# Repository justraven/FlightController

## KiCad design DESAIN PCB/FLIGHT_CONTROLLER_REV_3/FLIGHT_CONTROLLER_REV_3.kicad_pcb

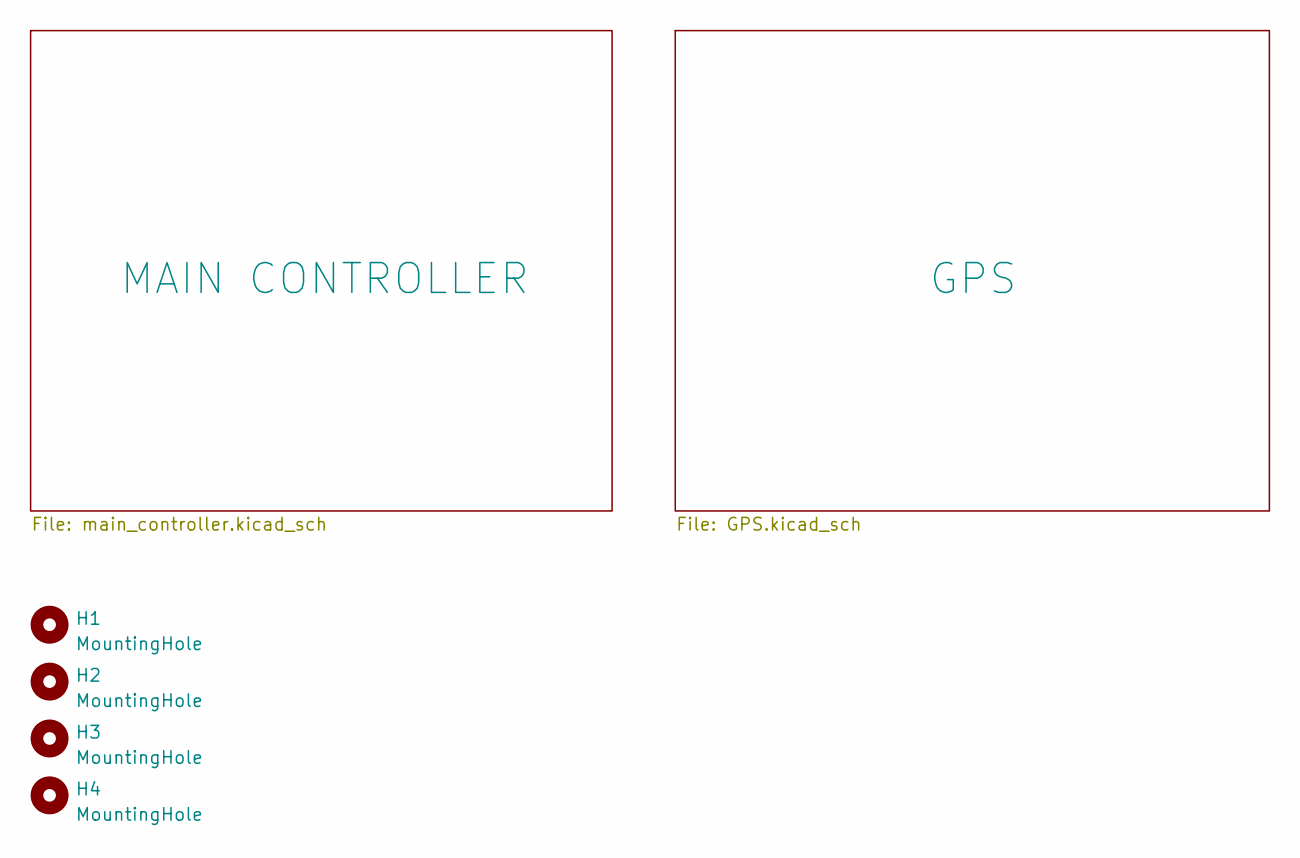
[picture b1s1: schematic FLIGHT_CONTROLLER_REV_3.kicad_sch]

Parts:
H1, H2, H3, H4: MountingHole; MountingHole_3.2mm_M3_Pad

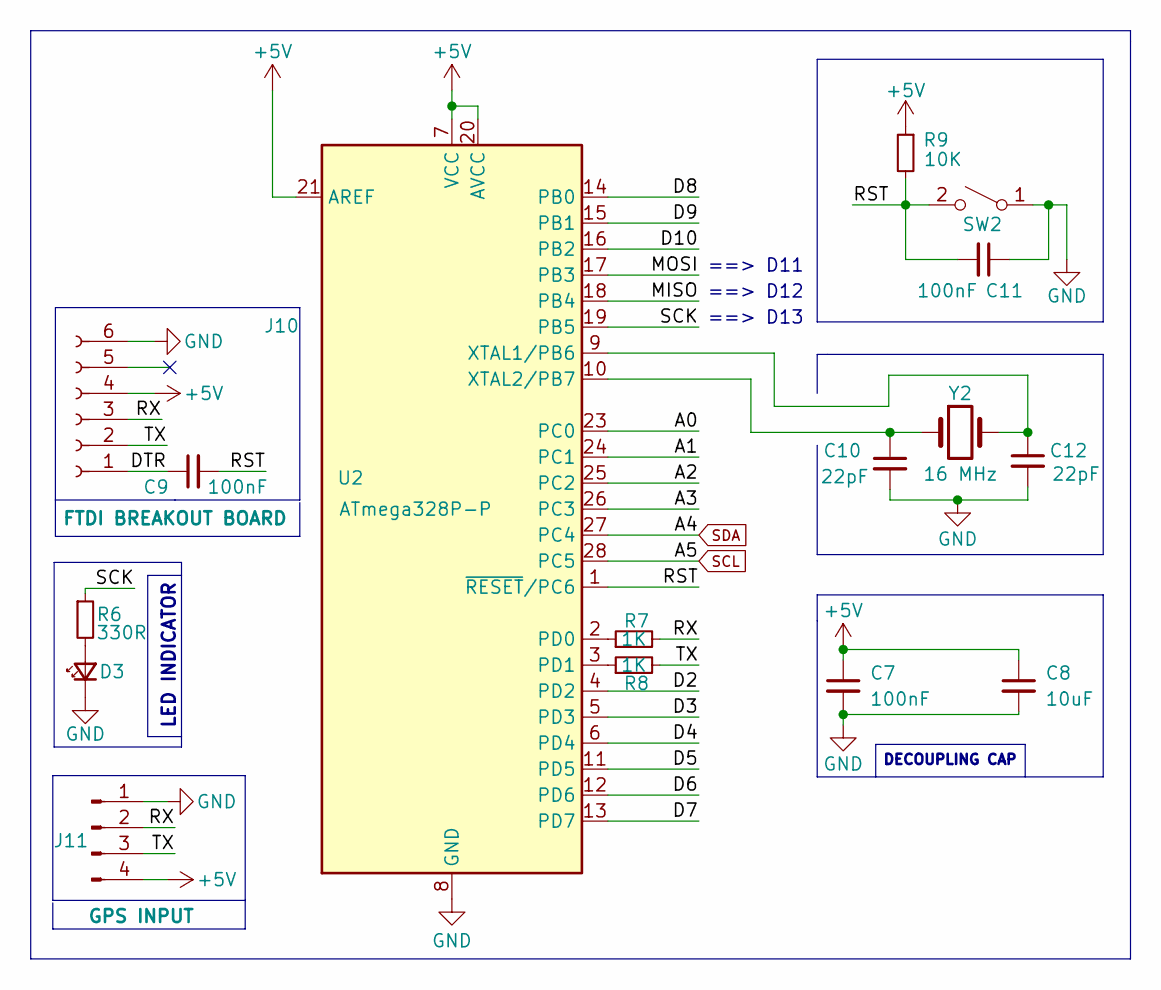
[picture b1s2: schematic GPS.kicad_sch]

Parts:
C7, C9, C11: 100nF; C_0805_2012Metric_Pad1.18x1.45mm_HandSolder
C8: 10uF; C_0805_2012Metric_Pad1.18x1.45mm_HandSolder
C10, C12: 22pF; C_0805_2012Metric_Pad1.18x1.45mm_HandSolder
D3: LED_Small; LED_D3.0mm
J10: FTDI BREAKOUT BOARD; PinSocket_1x06_P2.54mm_Vertical
J11: GPS INPUT; PinHeader_1x04_P2.54mm_Vertical
R6: 330R; R_0805_2012Metric_Pad1.20x1.40mm_HandSolder
R7, R8: 1K; R_0805_2012Metric_Pad1.20x1.40mm_HandSolder
R9: 10K; R_0805_2012Metric_Pad1.20x1.40mm_HandSolder
SW2: SW_SPST; SW_Tactile_SPST_Angled_PTS645Vx58-2LFS
U2: ATmega328P-P; DIP-28_W7.62mm
Y2: 16 MHz; Crystal_HC49-4H_Vertical

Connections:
+5V: C7.1, C8.1, J10.4, J11.4, R9.1, U2.7 (VCC), U2.20 (AVCC), U2.21 (AREF); also elsewhere on the board
/GPS/A0: U2.23 (PC0)
/GPS/A1: U2.24 (PC1)
/GPS/A2: U2.25 (PC2)
/GPS/A3: U2.26 (PC3)
/GPS/D2: U2.4 (PD2)
/GPS/D3: U2.5 (PD3)
/GPS/D4: U2.6 (PD4)
/GPS/D5: U2.11 (PD5)
/GPS/D6: U2.12 (PD6)
/GPS/D7: U2.13 (PD7)
/GPS/D8: U2.14 (PB0)
/GPS/D9: U2.15 (PB1)
/GPS/D10: U2.16 (PB2)
/GPS/DTR: C9.1, J10.1
/GPS/MISO: U2.18 (PB4)
/GPS/MOSI: U2.17 (PB3)
/GPS/RST: C9.2, C11.2, R9.2, SW2.2 (B), U2.1 (~RESET/PC6)
/GPS/RX: J10.3, J11.2, R7.2
/GPS/SCK: R6.1, U2.19 (PB5)
/GPS/TX: J10.2, J11.3, R8.2
GND: C7.2, C8.2, C10.2, C11.1, C12.2, D3.1 (K), J10.6, J11.1, SW2.1 (A), U2.8 (GND), U2.22 (GND); also elsewhere on the board
unnamed: D3.2 (A), R6.2
unnamed: R7.1, U2.2 (PD0)
unnamed: R8.1, U2.3 (PD1)
unnamed: C12.1, U2.9 (XTAL1/PB6), Y2.2
unnamed: C10.1, U2.10 (XTAL2/PB7), Y2.1
SCL: U2.28 (PC5); also elsewhere on the board
SDA: U2.27 (PC4); also elsewhere on the board

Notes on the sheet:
==> D12
==> D11
LED INDICATOR
DECOUPLING CAP
==> D13

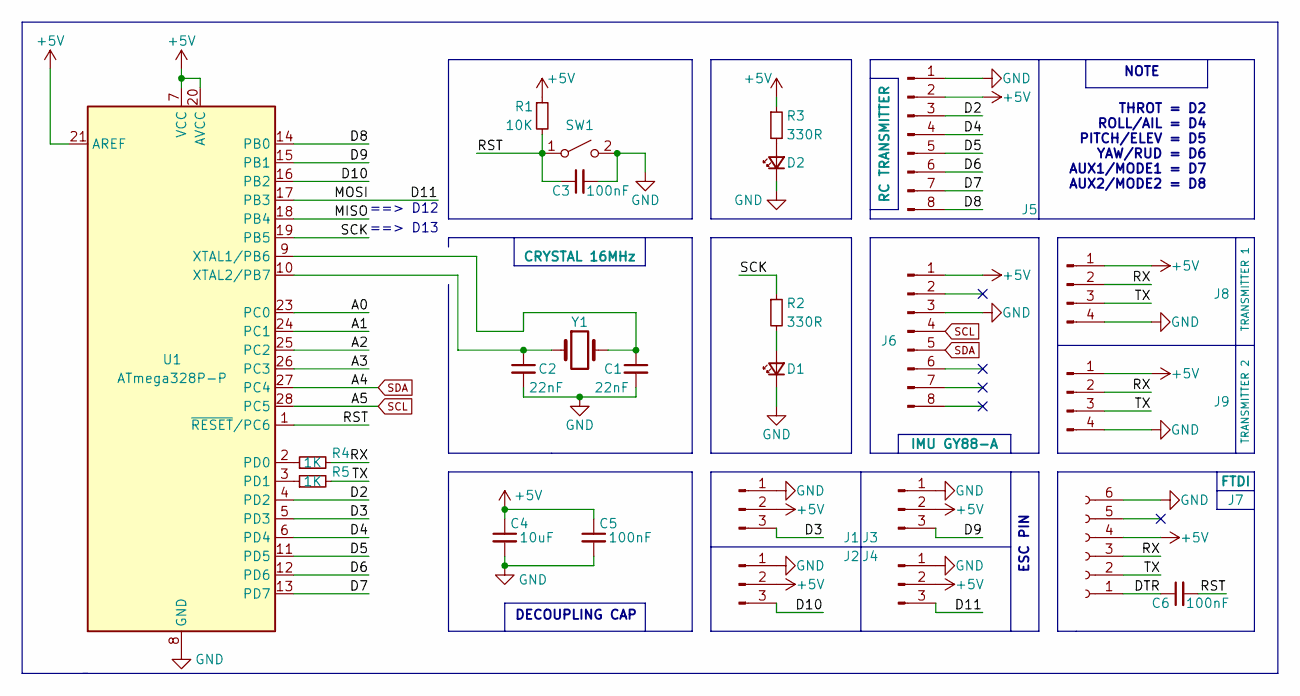
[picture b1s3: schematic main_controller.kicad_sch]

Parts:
C1, C2: 22nF; C_0805_2012Metric_Pad1.18x1.45mm_HandSolder
C3, C5, C6: 100nF; C_0805_2012Metric_Pad1.18x1.45mm_HandSolder
C4: 10uF; C_0805_2012Metric_Pad1.18x1.45mm_HandSolder
D1, D2: LED_Small; LED_D3.0mm
J1, J2, J3, J4: Conn_01x03_Pin; PinHeader_1x03_P2.54mm_Vertical
J5: RC TRANSMITTER; PinSocket_1x08_P2.54mm_Vertical
J6: IMU GY88-A; PinSocket_1x08_P2.54mm_Vertical
J7: FTDI; PinSocket_1x06_P2.54mm_Vertical
J8: TRANSMITTER 1; PinHeader_1x04_P2.54mm_Vertical
J9: TRANSMITTER 2; PinHeader_1x04_P2.54mm_Vertical
R1: 10K; R_0805_2012Metric_Pad1.20x1.40mm_HandSolder
R2, R3: 330R; R_0805_2012Metric_Pad1.20x1.40mm_HandSolder
R4, R5: 1K; R_0805_2012Metric_Pad1.20x1.40mm_HandSolder
SW1: SW_SPST; SW_Tactile_SPST_Angled_PTS645Vx58-2LFS
U1: ATmega328P-P; DIP-28_W7.62mm
Y1: CRYSTAL 16MHz; Crystal_HC49-4H_Vertical

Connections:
+5V: C4.1, C5.1, J1.2, J2.2, J3.2, J4.2, J5.2, J6.1, J7.4, J8.1, J9.1, R1.1, R3.1, U1.7 (VCC), U1.20 (AVCC), U1.21 (AREF); also elsewhere on the board
/MAIN CONTROLLER/A0: U1.23 (PC0)
/MAIN CONTROLLER/A1: U1.24 (PC1)
/MAIN CONTROLLER/A2: U1.25 (PC2)
/MAIN CONTROLLER/A3: U1.26 (PC3)
/MAIN CONTROLLER/D2: J5.3, U1.4 (PD2)
/MAIN CONTROLLER/D3: J1.3, U1.5 (PD3)
/MAIN CONTROLLER/D4: J5.4, U1.6 (PD4)
/MAIN CONTROLLER/D5: J5.5, U1.11 (PD5)
/MAIN CONTROLLER/D6: J5.6, U1.12 (PD6)
/MAIN CONTROLLER/D7: J5.7, U1.13 (PD7)
/MAIN CONTROLLER/D8: J5.8, U1.14 (PB0)
/MAIN CONTROLLER/D9: J3.3, U1.15 (PB1)
/MAIN CONTROLLER/D10: J2.3, U1.16 (PB2)
/MAIN CONTROLLER/D11: J4.3, U1.17 (PB3)
/MAIN CONTROLLER/DTR: C6.1, J7.1
/MAIN CONTROLLER/MISO: U1.18 (PB4)
/MAIN CONTROLLER/RST: C3.1, C6.2, R1.2, SW1.1 (A), U1.1 (~RESET/PC6)
/MAIN CONTROLLER/RX: J7.3, J8.2, J9.2, R4.2
/MAIN CONTROLLER/SCK: R2.1, U1.19 (PB5)
/MAIN CONTROLLER/TX: J7.2, J8.3, J9.3, R5.2
GND: C1.2, C2.2, C3.2, C4.2, C5.2, D1.1 (K), D2.1 (K), J1.1, J2.1, J3.1, J4.1, J5.1, J6.3, J7.6, J8.4, J9.4, SW1.2 (B), U1.8 (GND), U1.22 (GND); also elsewhere on the board
unnamed: D1.2 (A), R2.2
unnamed: D2.2 (A), R3.2
unnamed: R4.1, U1.2 (PD0)
unnamed: R5.1, U1.3 (PD1)
unnamed: C1.1, U1.9 (XTAL1/PB6), Y1.2
unnamed: C2.1, U1.10 (XTAL2/PB7), Y1.1
SCL: J6.4, U1.28 (PC5); also elsewhere on the board
SDA: J6.5, U1.27 (PC4); also elsewhere on the board

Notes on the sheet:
NOTE
DECOUPLING CAP
THROT = D2 ROLL/AIL = D4 PITCH/ELEV = D5 YAW/RUD = D6 AUX1/MODE1 = D7 AUX2/MODE2 = D8
==> D12
ESC PIN
==> D13

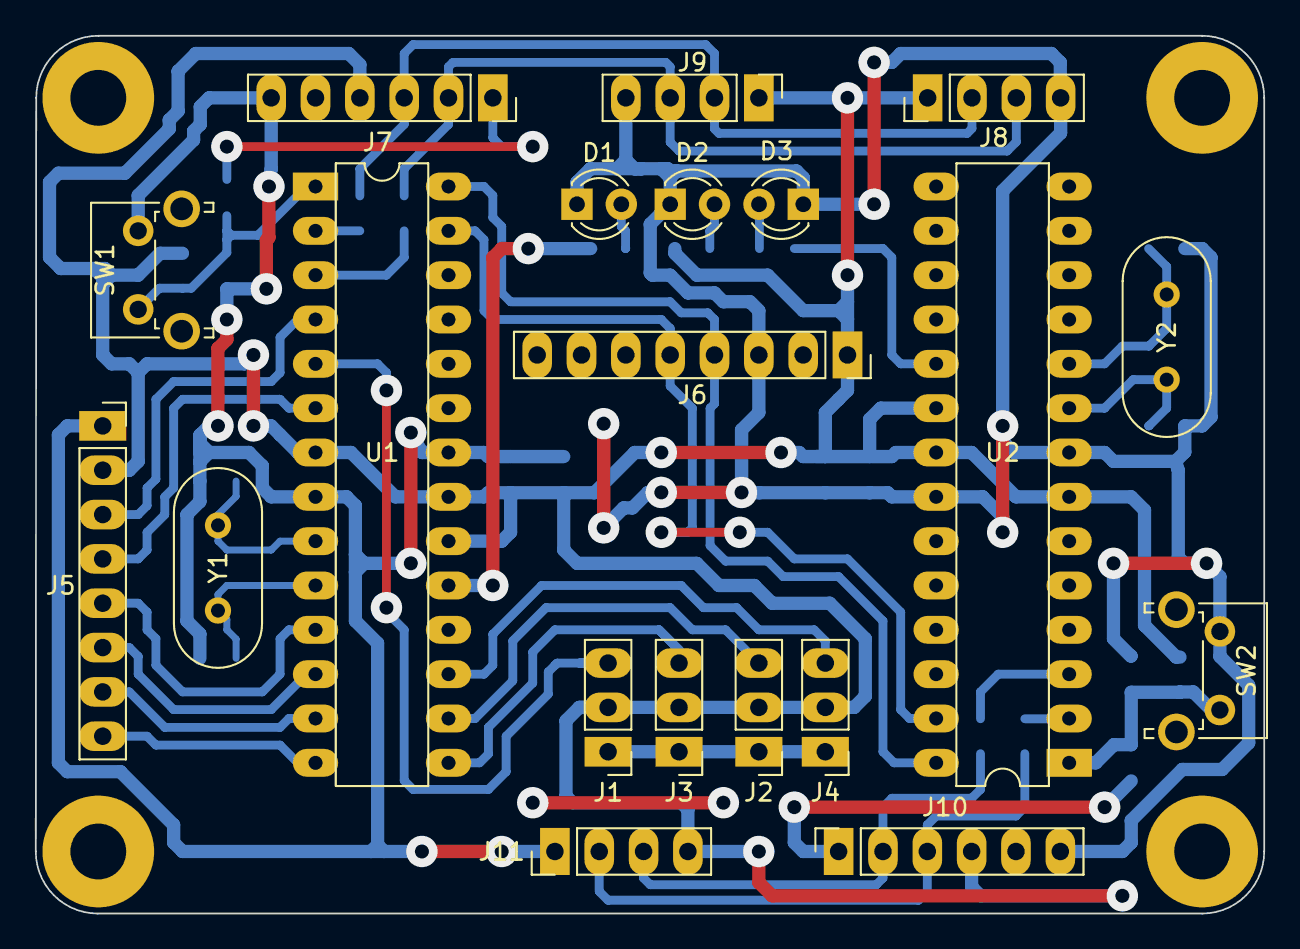
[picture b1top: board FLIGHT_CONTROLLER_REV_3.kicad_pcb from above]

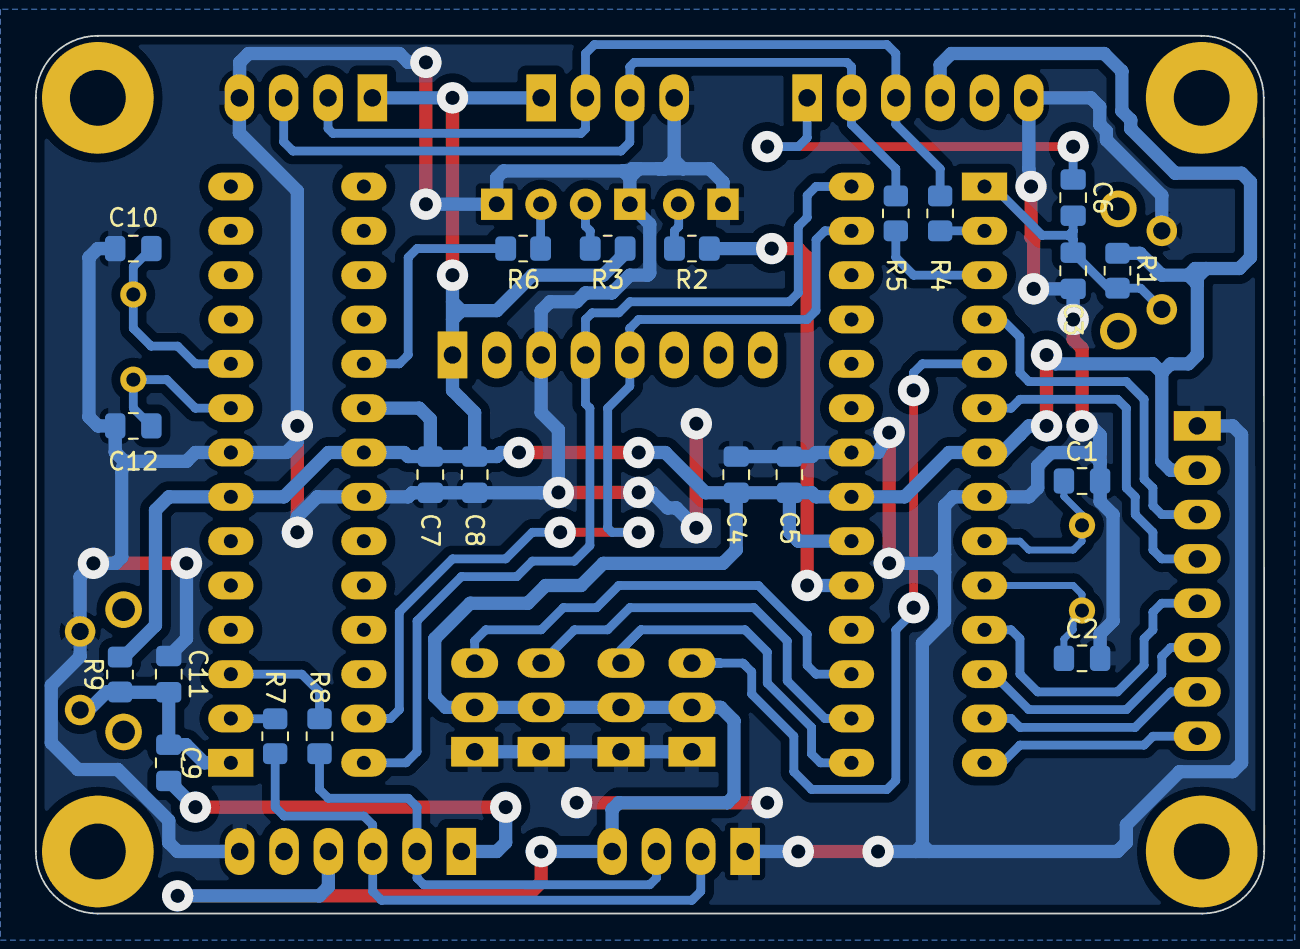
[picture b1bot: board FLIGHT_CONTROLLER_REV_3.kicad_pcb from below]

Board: 2 copper layers, 70.4 x 50.3 mm, 45 parts (21 on the bottom side), 35 nets.

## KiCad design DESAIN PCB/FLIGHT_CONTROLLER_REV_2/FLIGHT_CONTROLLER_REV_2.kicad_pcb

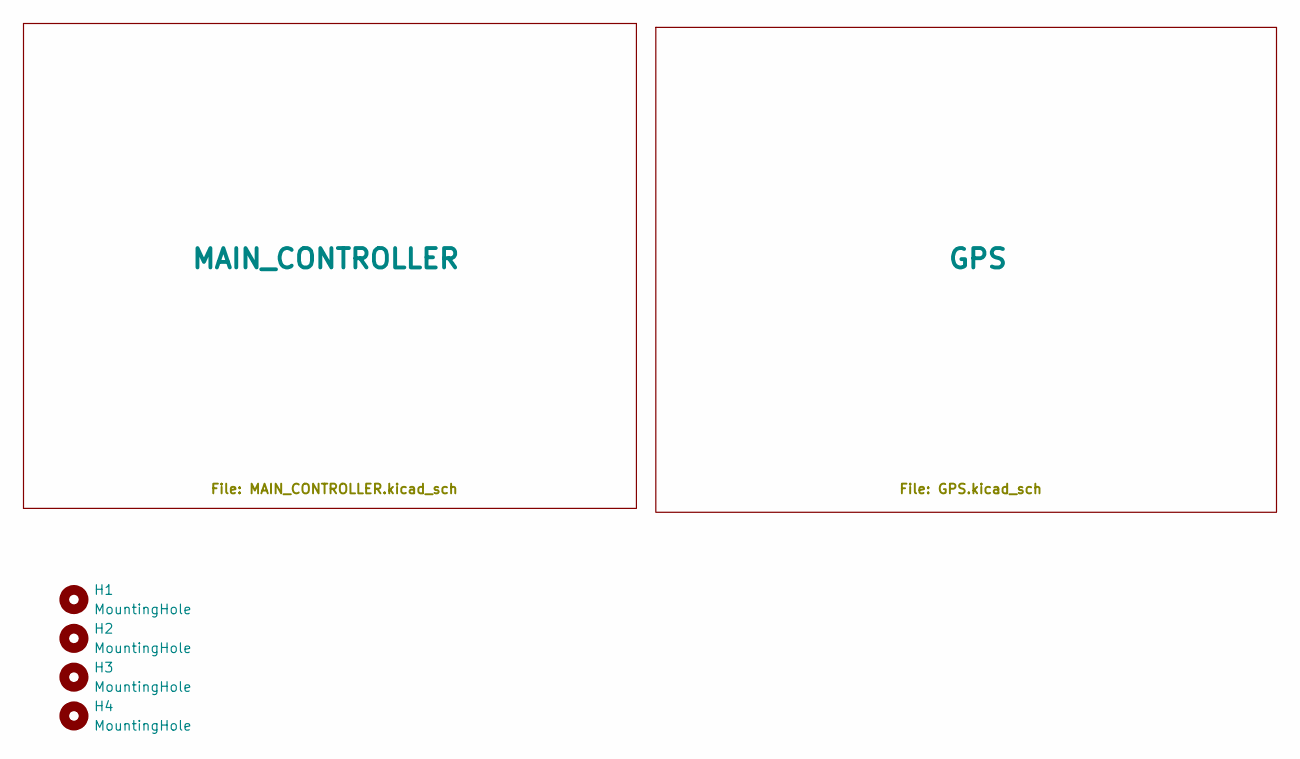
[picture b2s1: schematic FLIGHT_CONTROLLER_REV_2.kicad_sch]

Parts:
H1, H2, H3, H4: MountingHole; MountingHole_3.2mm_M3_ISO7380_Pad

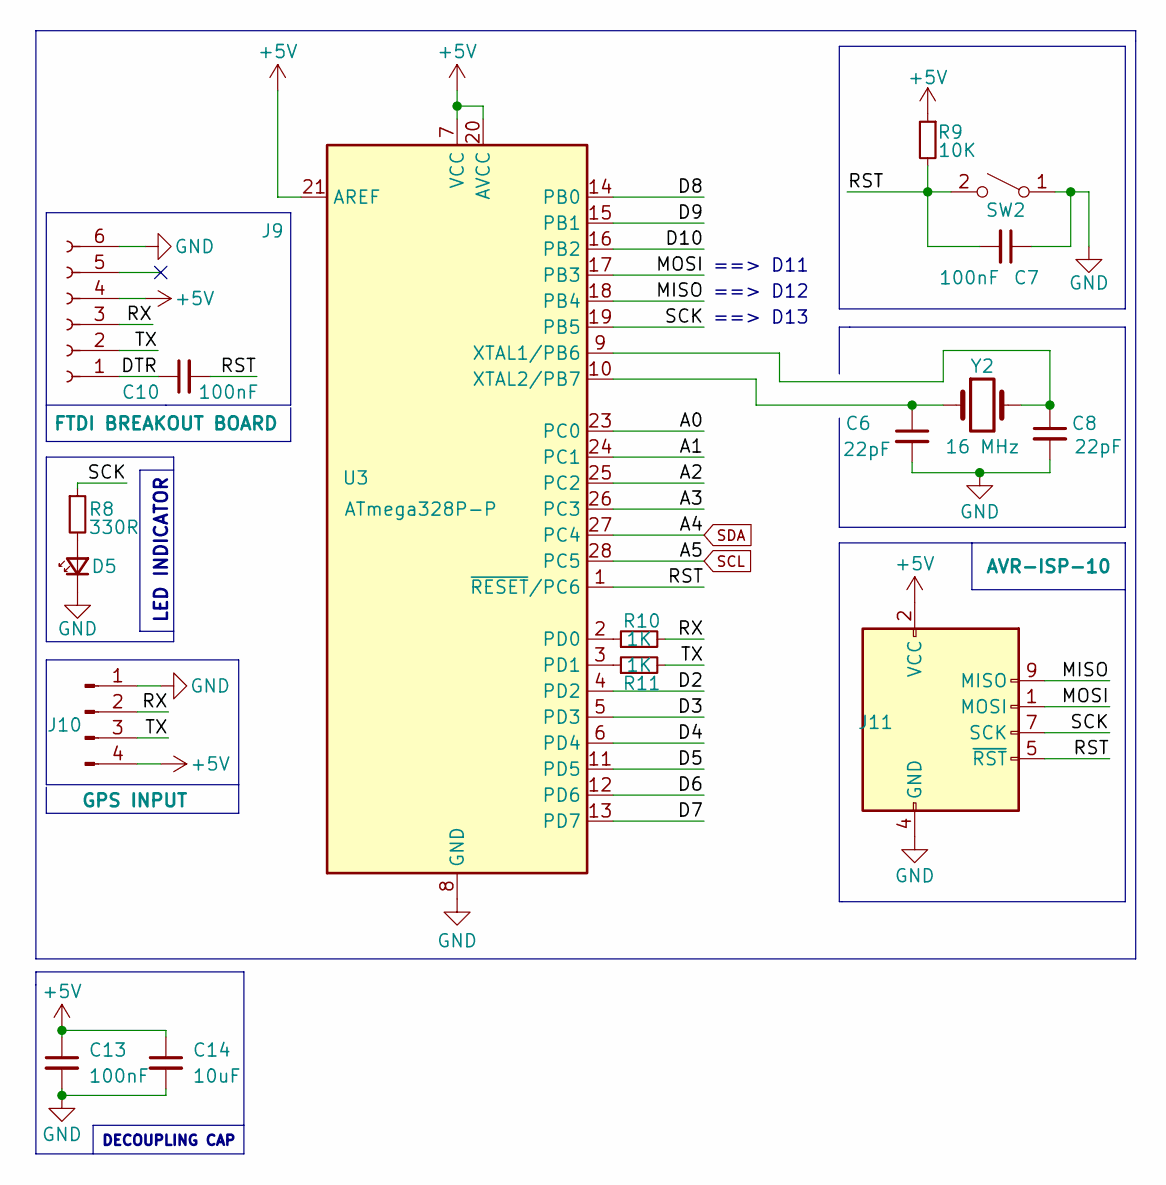
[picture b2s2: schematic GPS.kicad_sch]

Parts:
C6, C8: 22pF; C_Disc_D5.0mm_W2.5mm_P2.50mm
C7, C10, C13: 100nF; C_Disc_D5.0mm_W2.5mm_P2.50mm
C14: 10uF; C_Disc_D5.0mm_W2.5mm_P2.50mm
D5: LED_Small; LED_D3.0mm
J9: FTDI BREAKOUT BOARD; PinSocket_1x06_P2.54mm_Vertical
J10: GPS INPUT; PinHeader_1x04_P2.54mm_Vertical
J11: AVR-ISP-10; IDC-Header_2x05_P2.54mm_Vertical
R8: 330R; R_Axial_DIN0207_L6.3mm_D2.5mm_P7.62mm_Horizontal
R9: 10K; R_Axial_DIN0207_L6.3mm_D2.5mm_P7.62mm_Horizontal
R10, R11: 1K; R_Axial_DIN0207_L6.3mm_D2.5mm_P7.62mm_Horizontal
SW2: SW_SPST; SW_Tactile_SPST_Angled_PTS645Vx58-2LFS
U3: ATmega328P-P; DIP-28_W7.62mm
Y2: 16 MHz; Crystal_HC49-4H_Vertical

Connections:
+5V: C13.1, C14.1, J9.4, J10.4, J11.2 (VCC), R9.1, U3.7 (VCC), U3.20 (AVCC), U3.21 (AREF); also elsewhere on the board
/GPS/A0: U3.23 (PC0)
/GPS/A1: U3.24 (PC1)
/GPS/A2: U3.25 (PC2)
/GPS/A3: U3.26 (PC3)
/GPS/D2: U3.4 (PD2)
/GPS/D3: U3.5 (PD3)
/GPS/D4: U3.6 (PD4)
/GPS/D5: U3.11 (PD5)
/GPS/D6: U3.12 (PD6)
/GPS/D7: U3.13 (PD7)
/GPS/D8: U3.14 (PB0)
/GPS/D9: U3.15 (PB1)
/GPS/D10: U3.16 (PB2)
/GPS/DTR: C10.1, J9.1
/GPS/MISO: J11.9 (MISO), U3.18 (PB4)
/GPS/MOSI: J11.1 (MOSI), U3.17 (PB3)
/GPS/RST: C7.2, C10.2, J11.5 (~RST), R9.2, SW2.2 (B), U3.1 (~RESET/PC6)
/GPS/RX: J9.3, J10.2, R10.2
/GPS/SCK: J11.7 (SCK), R8.1, U3.19 (PB5)
/GPS/TX: J9.2, J10.3, R11.2
GND: C6.2, C7.1, C8.2, C13.2, C14.2, D5.1 (K), J9.6, J10.1, J11.4 (GND), J11.6 (GND), J11.8 (GND), J11.10 (GND), SW2.1 (A), U3.8 (GND), U3.22 (GND); also elsewhere on the board
unnamed: C6.1, U3.10 (XTAL2/PB7), Y2.1
unnamed: C8.1, U3.9 (XTAL1/PB6), Y2.2
unnamed: D5.2 (A), R8.2
unnamed: R10.1, U3.2 (PD0)
unnamed: R11.1, U3.3 (PD1)
SCL: U3.28 (PC5); also elsewhere on the board
SDA: U3.27 (PC4); also elsewhere on the board

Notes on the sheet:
DECOUPLING CAP
==> D13
==> D11
==> D12
LED INDICATOR

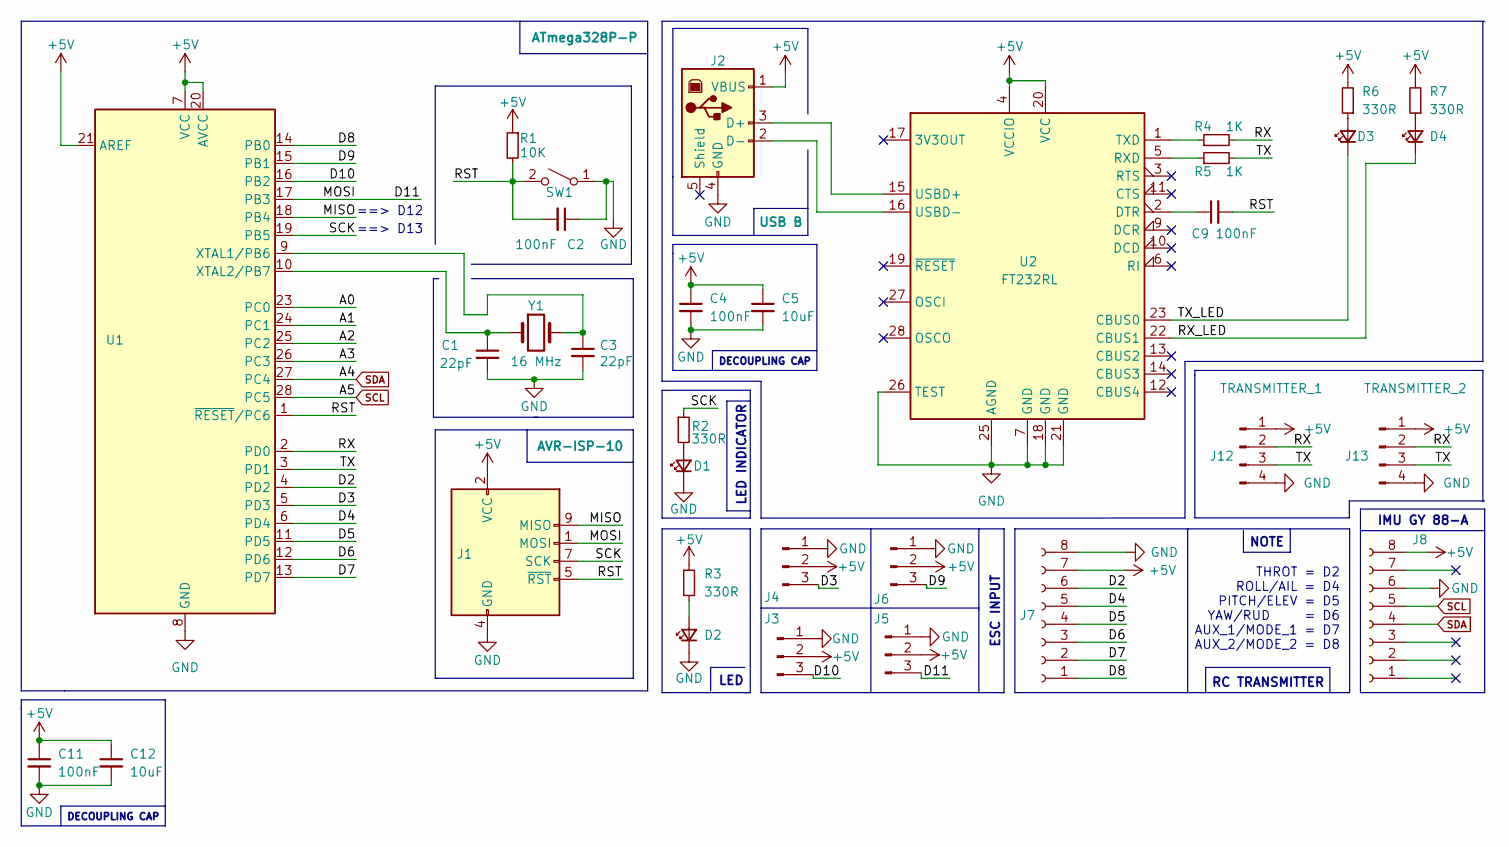
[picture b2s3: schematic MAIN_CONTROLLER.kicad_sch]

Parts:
C1, C3: 22pF; C_Disc_D5.0mm_W2.5mm_P2.50mm
C2, C4, C9, C11: 100nF; C_Disc_D5.0mm_W2.5mm_P2.50mm
C5, C12: 10uF; C_Disc_D5.0mm_W2.5mm_P2.50mm
D1, D2, D3, D4: LED_Small; LED_D3.0mm
J1: AVR-ISP-10; IDC-Header_2x05_P2.54mm_Vertical
J2: USB B; USB_B_Lumberg_2411_02_Horizontal
J3, J4, J5, J6: Conn_01x03_Male; PinHeader_1x03_P2.54mm_Vertical
J7, J8: Conn_01x08_Female; PinSocket_1x08_P2.54mm_Vertical
J12: TRANSMITTER_1; PinHeader_1x04_P2.54mm_Vertical
J13: TRANSMITTER_2; PinHeader_1x04_P2.54mm_Vertical
R1: 10K; R_Axial_DIN0207_L6.3mm_D2.5mm_P7.62mm_Horizontal
R2, R3, R6, R7: 330R; R_Axial_DIN0207_L6.3mm_D2.5mm_P7.62mm_Horizontal
R4, R5: 1K; R_Axial_DIN0207_L6.3mm_D2.5mm_P7.62mm_Horizontal
SW1: SW_SPST; SW_Tactile_SPST_Angled_PTS645Vx58-2LFS
U1: ATmega328P-P; DIP-28_W7.62mm
U2: FT232RL; SSOP-28_5.3x10.2mm_P0.65mm
Y1: 16 MHz; Crystal_HC49-4H_Vertical

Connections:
+5V: C4.1, C5.1, C11.1, C12.1, J1.2 (VCC), J2.1 (VBUS), J3.2, J4.2, J5.2, J6.2, J7.7, J8.8, J12.1, J13.1, R1.1, R3.1, R6.2, R7.2, U1.7 (VCC), U1.20 (AVCC), U1.21 (AREF), U2.4 (VCCIO), U2.20 (VCC); also elsewhere on the board
/MAIN_CONTROLLER/A0: U1.23 (PC0)
/MAIN_CONTROLLER/A1: U1.24 (PC1)
/MAIN_CONTROLLER/A2: U1.25 (PC2)
/MAIN_CONTROLLER/A3: U1.26 (PC3)
/MAIN_CONTROLLER/D2: J7.6, U1.4 (PD2)
/MAIN_CONTROLLER/D3: J4.3, U1.5 (PD3)
/MAIN_CONTROLLER/D4: J7.5, U1.6 (PD4)
/MAIN_CONTROLLER/D5: J7.4, U1.11 (PD5)
/MAIN_CONTROLLER/D6: J7.3, U1.12 (PD6)
/MAIN_CONTROLLER/D7: J7.2, U1.13 (PD7)
/MAIN_CONTROLLER/D8: J7.1, U1.14 (PB0)
/MAIN_CONTROLLER/D9: J6.3, U1.15 (PB1)
/MAIN_CONTROLLER/D10: J3.3, U1.16 (PB2)
/MAIN_CONTROLLER/D11: J1.1 (MOSI), J5.3, U1.17 (PB3)
/MAIN_CONTROLLER/MISO: J1.9 (MISO), U1.18 (PB4)
/MAIN_CONTROLLER/RST: C2.2, C9.2, J1.5 (~RST), R1.2, SW1.2 (B), U1.1 (~RESET/PC6)
/MAIN_CONTROLLER/RX: J12.2, J13.2, R4.2, U1.2 (PD0)
/MAIN_CONTROLLER/RX_LED: D4.1 (K), U2.22 (CBUS1)
/MAIN_CONTROLLER/SCK: J1.7 (SCK), R2.1, U1.19 (PB5)
/MAIN_CONTROLLER/TX: J12.3, J13.3, R5.2, U1.3 (PD1)
/MAIN_CONTROLLER/TX_LED: D3.1 (K), U2.23 (CBUS0)
GND: C1.2, C2.1, C3.2, C4.2, C5.2, C11.2, C12.2, D1.1 (K), D2.1 (K), J1.4 (GND), J1.6 (GND), J1.8 (GND), J1.10 (GND), J2.4 (GND), J3.1, J4.1, J5.1, J6.1, J7.8, J8.6, J12.4, J13.4, SW1.1 (A), U1.8 (GND), U1.22 (GND), U2.7 (GND), U2.18 (GND), U2.21 (GND), U2.25 (AGND), U2.26 (TEST); also elsewhere on the board
unnamed: C1.1, U1.10 (XTAL2/PB7), Y1.1
unnamed: C3.1, U1.9 (XTAL1/PB6), Y1.2
unnamed: C9.1, U2.2 (DTR)
unnamed: D1.2 (A), R2.2
unnamed: D2.2 (A), R3.2
unnamed: D3.2 (A), R6.1
unnamed: D4.2 (A), R7.1
unnamed: J2.2 (D-), U2.16 (USBD-)
unnamed: J2.3 (D+), U2.15 (USBD+)
unnamed: R4.1, U2.1 (TXD)
unnamed: R5.1, U2.5 (RXD)
SCL: J8.5, U1.28 (PC5); also elsewhere on the board
SDA: J8.4, U1.27 (PC4); also elsewhere on the board

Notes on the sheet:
ESC INPUT
NOTE
==> D12
RC TRANSMITTER
LED
IMU GY 88-A
DECOUPLING CAP
==> D13
LED INDICATOR
THROT = D2 ROLL/AIL = D4 PITCH/ELEV = D5 YAW/RUD = D6 AUX_1/MODE_1 = D7 AUX_2/MODE_2 = D8

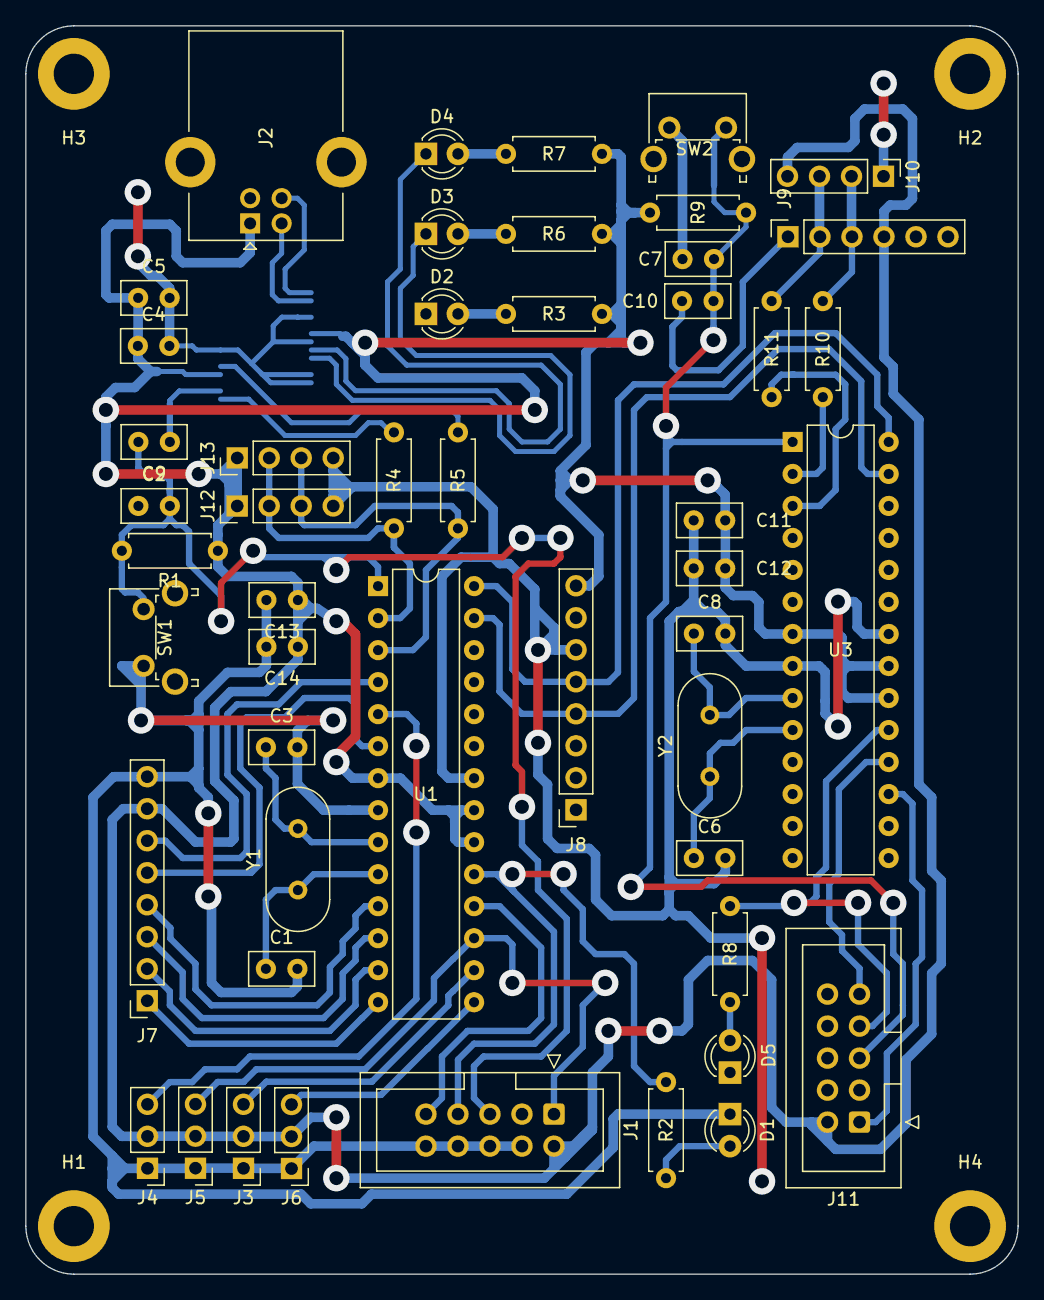
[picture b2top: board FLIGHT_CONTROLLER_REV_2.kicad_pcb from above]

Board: 2 copper layers, 78.7 x 99.1 mm, 54 parts (1 on the bottom side), 44 nets.

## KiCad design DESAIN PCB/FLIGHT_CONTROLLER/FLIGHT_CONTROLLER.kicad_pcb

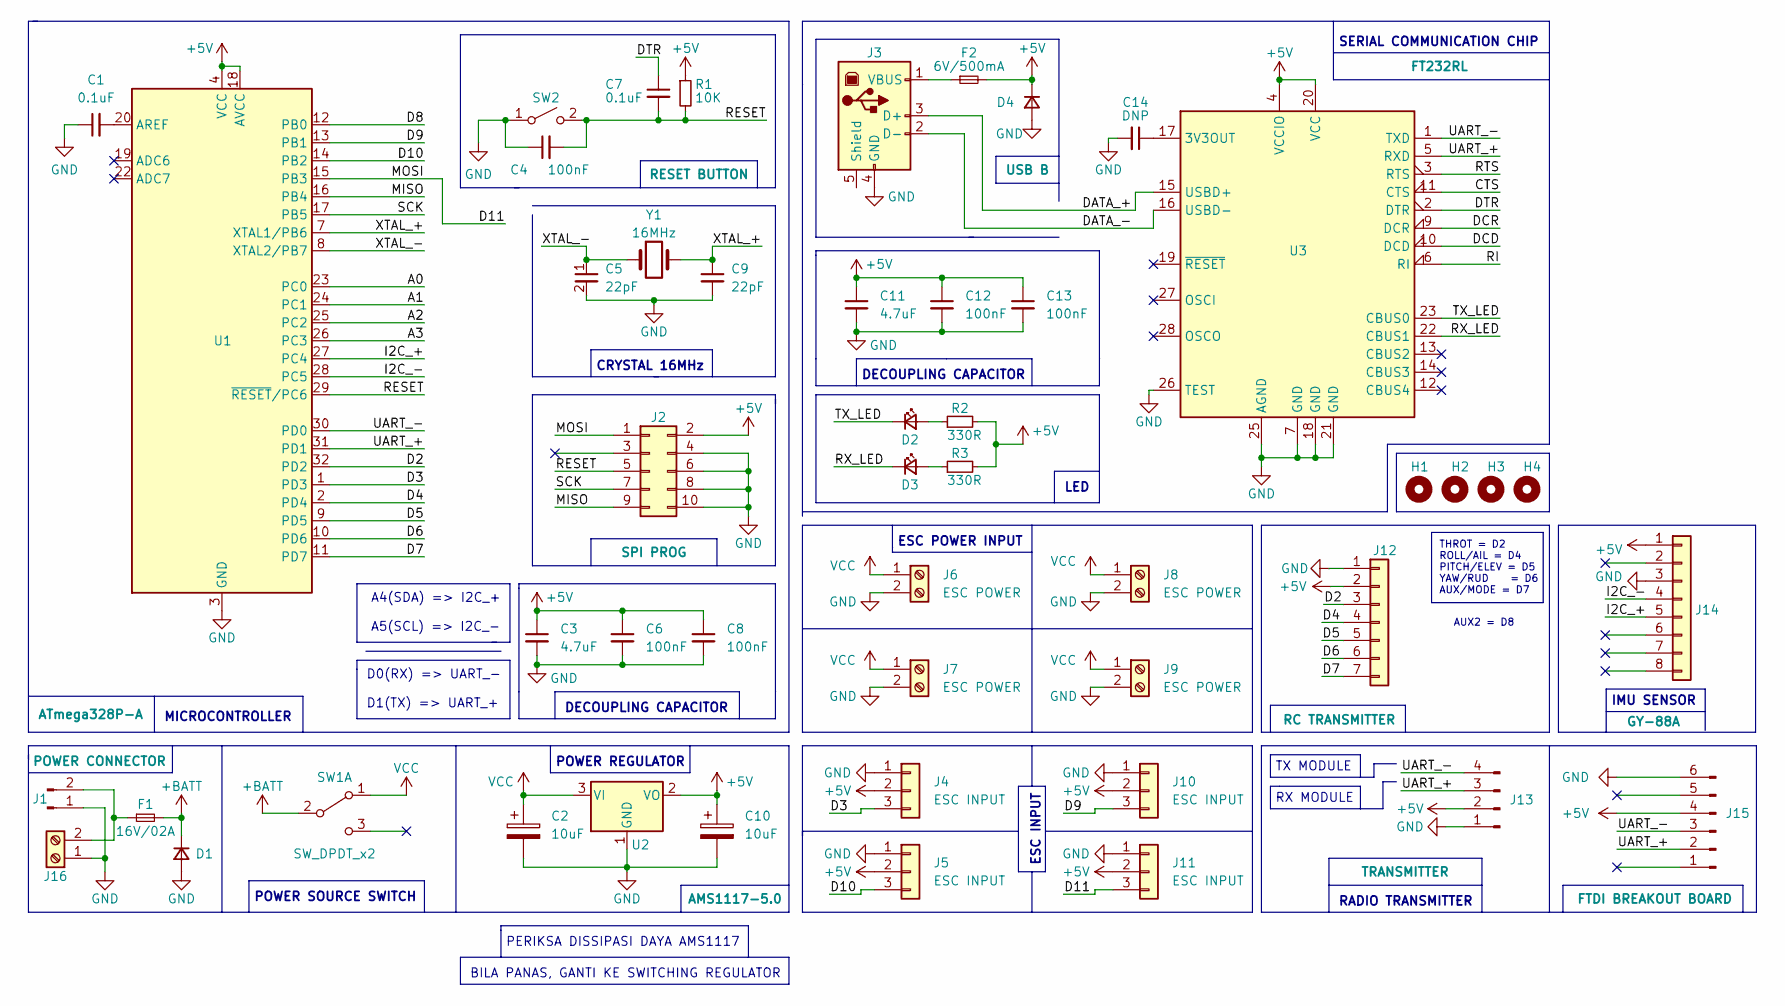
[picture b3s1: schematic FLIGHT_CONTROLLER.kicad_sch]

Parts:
C1, C7: 0.1uF; C_0805_2012Metric_Pad1.18x1.45mm_HandSolder
C2, C10: 10uF; CP_EIA-3216-18_Kemet-A_Pad1.58x1.35mm_HandSolder
C3, C11: 4.7uF; C_0805_2012Metric_Pad1.18x1.45mm_HandSolder
C4, C6, C8, C12, C13: 100nF; C_0805_2012Metric_Pad1.18x1.45mm_HandSolder
C5, C9: 22pF; C_0805_2012Metric_Pad1.18x1.45mm_HandSolder
C14: DNP; C_0805_2012Metric_Pad1.18x1.45mm_HandSolder
D1, D4: D_Small; D_SMB_Handsoldering
D2, D3: LED_Small; LED_0805_2012Metric_Pad1.15x1.40mm_HandSolder
F1: 16V/02A; Fuse_1812_4532Metric_Pad1.30x3.40mm_HandSolder
F2: 6V/500mA; Fuse_1812_4532Metric_Pad1.30x3.40mm_HandSolder
H1, H2, H3, H4: MountingHole; MountingHole_3.2mm_M3_ISO14580_Pad
J1: POWER CONNECTOR; AMASS_XT60-M_1x02_P7.20mm_Vertical
J2: SPI PROG; IDC-Header_2x05_P2.54mm_Vertical
J3: USB B; USB_B_Lumberg_2411_02_Horizontal
J4, J5, J10, J11: ESC INPUT; PinSocket_1x03_P2.54mm_Vertical
J6, J7, J8, J9, J16: ESC POWER; TerminalBlock_Phoenix_MKDS-1,5-2-5.08_1x02_P5.08mm_Horizont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
J12: RC TRANSMITTER; PinSocket_1x07_P2.54mm_Vertical
J13: TRANSMITTER; PinSocket_1x04_P2.54mm_Vertical
J14: GY-88A; PinSocket_1x08_P2.54mm_Vertical
J15: FTDI BREAKOUT BOARD; PinSocket_1x06_P2.54mm_Vertical
R1: 10K; R_0805_2012Metric_Pad1.20x1.40mm_HandSolder
R2, R3: 330R; R_0805_2012Metric_Pad1.20x1.40mm_HandSolder
SW1: SW_DPDT_x2; SW_Push_2P2T_Toggle_CK_PVA2xxH4xxxxxxV2
SW2: RESET BUTTON; SW_Tactile_SPST_Angled_PTS645Vx31-2LFS
U1: ATmega328P-A; TQFP-32_7x7mm_P0.8mm
U2: AMS1117-5.0; SOT-223-3_TabPin2
U3: FT232RL; SSOP-28_5.3x10.2mm_P0.65mm
Y1: 16MHz; Crystal_HC49-4H_Vertical

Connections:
+5V: C3.1, C6.1, C8.1, C10.1, C11.1, C12.1, C13.1, D4.1 (K), F2.2, J2.2, J4.2, J5.2, J10.2, J11.2, J12.2, J13.2, J14.1, J15.4, R1.1, R2.2, R3.2, U1.4 (VCC), U1.6 (VCC), U1.18 (AVCC), U2.2 (VO), U3.4 (VCCIO), U3.20 (VCC)
+BATT: D1.1 (K), F1.2, SW1.2 (B)
/A0: U1.23 (PC0)
/A1: U1.24 (PC1)
/A2: U1.25 (PC2)
/A3: U1.26 (PC3)
/CTS: U3.11 (CTS)
/D2: J12.3, U1.32 (PD2)
/D3: J4.3, U1.1 (PD3)
/D4: J12.4, U1.2 (PD4)
/D5: J12.5, U1.9 (PD5)
/D6: J12.6, U1.10 (PD6)
/D7: J12.7, U1.11 (PD7)
/D8: U1.12 (PB0)
/D9: J10.3, U1.13 (PB1)
/D10: J5.3, U1.14 (PB2)
/D11: J2.1, J11.3, U1.15 (PB3)
/DATA_+: J3.3 (D+), U3.15 (USBD+)
/DATA_-: J3.2 (D-), U3.16 (USBD-)
/DCD: U3.10 (DCD)
/DCR: U3.9 (DCR)
/DTR: C7.1, U3.2 (DTR)
/I2C_+: J14.5, U1.27 (PC4)
/I2C_-: J14.4, U1.28 (PC5)
/MISO: J2.9, U1.16 (PB4)
/RESET: C4.2, C7.2, J2.5, R1.2, SW2.2 (B), U1.29 (~RESET/PC6)
/RI: U3.6 (RI)
/RTS: U3.3 (RTS)
/RX_LED: D3.1 (K), U3.22 (CBUS1)
/SCK: J2.7, U1.17 (PB5)
/TX_LED: D2.1 (K), U3.23 (CBUS0)
/UART_+: J13.3, J15.2, U1.31 (PD1), U3.5 (RXD)
/UART_-: J13.4, J15.3, U1.30 (PD0), U3.1 (TXD)
/XTAL_+: C9.1, U1.7 (XTAL1/PB6), Y1.2
/XTAL_-: C5.1, U1.8 (XTAL2/PB7), Y1.1
GND: C1.1, C2.2, C3.2, C4.1, C5.2, C6.2, C8.2, C9.2, C10.2, C11.2, C12.2, C13.2, C14.2, D1.2 (A), D4.2 (A), J1.1, J2.4, J2.6, J2.8, J2.10, J3.4 (GND), J4.1, J5.1, J6.2, J7.2, J8.2, J9.2, J10.1, J11.1, J12.1, J13.1, J14.3, J15.6, J16.1, SW2.1 (A), U1.3 (GND), U1.5 (GND), U1.21 (GND), U2.1 (GND), U3.7 (GND), U3.18 (GND), U3.21 (GND), U3.25 (AGND), U3.26 (TEST)
unnamed: C1.2, U1.20 (AREF)
unnamed: C14.1, U3.17 (3V3OUT)
unnamed: D2.2 (A), R2.1
unnamed: D3.2 (A), R3.1
unnamed: F1.1, J1.2, J16.2
unnamed: F2.1, J3.1 (VBUS)
VCC: C2.1, J6.1, J7.1, J8.1, J9.1, SW1.1 (A), U2.3 (VI)

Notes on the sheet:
ESC INPUT
D0(RX) => UART_- D1(TX) => UART_+
AUX2 = D8
DECOUPLING CAPACITOR
LED
TX MODULE
PERIKSA DISSIPASI DAYA AMS1117
RADIO TRANSMITTER
BILA PANAS, GANTI KE SWITCHING REGULATOR
ESC POWER INPUT
THROT = D2 ROLL/AIL = D4 PITCH/ELEV = D5 YAW/RUD = D6 AUX/MODE = D7
MICROCONTROLLER
RX MODULE
A4(SDA) => I2C_+ A5(SCL) => I2C_-
POWER SOURCE SWITCH
SERIAL COMMUNICATION CHIP
IMU SENSOR
POWER REGULATOR
CRYSTAL 16MHz
